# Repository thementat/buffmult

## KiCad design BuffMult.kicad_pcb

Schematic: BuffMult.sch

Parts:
C1, C2, C3, C4: 6p; C_0805_2012Metric
C5, C6, C7, C8, C9, C10, C11, C12, C13, C14, C15, C16: 10p; C_0805_2012Metric
C17, C22: 22u; CP_Elec_5x5.8
C18, C19, C20, C21, C23, C24, C25, C26: 100n; C_0805_2012Metric
D1, D2: 1N5819HW; D_SOD-123
J1, J2: Conn_01x01; PinHeader_1x01_P2.54mm_Vertical
J3: Conn_02x05_Odd_Even; PinHeader_2x05_P2.54mm_Vertical_SMD
JP1, JP2, JP3, JP4, JP5, JP6, JP7, JP8, JP9, JP10, JP11, JP12, JP13, JP14, JP15: SolderJumper; SolderJumper-2_P1.3mm_Open_TrianglePad1.0x1.5mm
R1, R2, R3, R4: 107k; C_0805_2012Metric
R5, R6, R7, R8: 100k; C_0805_2012Metric
R9, R10, R11, R12, R13, R14, R15, R16, R25, R26, R27, R28, R29, R30, R31, R32, R41, R42, R43, R44, R45, R46, R47, R48: 49.9k; C_0805_2012Metric
R17, R18, R19, R20, R33, R34, R35, R36, R49, R50, R51, R52: 301; C_0805_2012Metric
R21, R22, R23, R24, R37, R38, R39, R40, R53, R54, R55, R56: 13.3k; C_0805_2012Metric
RV1, RV2, RV3, RV4, RV5, RV6, RV7, RV8, RV9, RV10, RV11, RV12: R_POT_US; Potentiometer_Bourns_3296W_Vertical
U1: PJ-301BM; WQP-PJ301M-12_JACK
U2, U4, U6, U8: TL074; SOIC-14_3.9x8.7mm_P1.27mm
U3, U5, U7, U9, U10, U11, U12, U16, U20: PJ-301BM; PJ301M
U13, U14, U15, U17, U18, U19: PJ-301BM; PJ301M-NG

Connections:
+12V: C17.1, C18.1, C19.1, C20.1, C21.1, D1.1, U2.4 (V+), U4.4 (V+), U6.4 (V+), U8.4 (V+)
-12V: C22.2, C23.2, C24.2, C25.2, C26.2, D2.2, U2.11 (V-), U4.11 (V-), U6.11 (V-), U8.11 (V-)
Earth: C17.2, C18.2, C19.2, C20.2, C21.2, C22.1, C23.1, C24.1, C25.1, C26.1, J1.1, J2.1, J3.3, J3.4, J3.5, J3.6, J3.7, J3.8, R21.2, R22.2, R23.2, R24.2, R37.2, R38.2, R39.2, R40.2, R53.2, R54.2, R55.2, R56.2, U1.P$3, U2.3 (+), U2.5 (+), U2.10 (+), U2.12 (+), U3.P$3, U4.3 (+), U4.5 (+), U4.10 (+), U4.12 (+), U5.P$3, U6.3 (+), U6.5 (+), U6.10 (+), U6.12 (+), U7.P$3, U8.3 (+), U8.5 (+), U8.10 (+), U8.12 (+), U9.P$3, U10.P$3, U11.P$3, U12.P$3, U16.P$3, U20.P$3
unnamed: C1.1, R1.1, RV1.1, RV5.1, RV9.1, U2.14
unnamed: C1.2, R1.2, R5.1, U2.13 (-)
unnamed: C2.1, R2.1, RV2.1, RV6.1, RV10.1, U4.14
unnamed: C2.2, R2.2, R6.1, U4.13 (-)
unnamed: C3.1, R3.1, RV3.1, RV7.1, RV11.1, U6.14
unnamed: C3.2, R3.2, R7.1, U6.13 (-)
unnamed: C4.1, R4.1, RV4.1, RV8.1, RV12.1, U8.14
unnamed: C4.2, R4.2, R8.1, U8.13 (-)
unnamed: C5.1, R17.2, U2.1
unnamed: C5.2, R9.2, R13.1, U2.2 (-)
unnamed: C6.1, R18.2, U4.1
unnamed: C6.2, R10.2, R14.1, U4.2 (-)
unnamed: C7.1, R19.2, U6.1
unnamed: C7.2, R11.2, R15.1, U6.2 (-)
unnamed: C8.1, R20.2, U8.1
unnamed: C8.2, R12.2, R16.1, U8.2 (-)
unnamed: C9.1, R33.2, U2.8
unnamed: C9.2, R25.2, R29.1, U2.9 (-)
unnamed: C10.1, R34.2, U4.8
unnamed: C10.2, R26.2, R30.1, U4.9 (-)
unnamed: C11.1, R35.2, U6.8
unnamed: C11.2, R27.2, R31.1, U6.9 (-)
unnamed: C12.1, R36.2, U8.8
unnamed: C12.2, R28.2, R32.1, U8.9 (-)
unnamed: C13.1, R49.2, U2.7
unnamed: C13.2, R41.2, R45.1, U2.6 (-)
unnamed: C14.1, R50.2, U4.7
unnamed: C14.2, R42.2, R46.1, U4.6 (-)
unnamed: C15.1, R51.2, U6.7
unnamed: C15.2, R43.2, R47.1, U6.6 (-)
unnamed: C16.1, R52.2, U8.7
unnamed: C16.2, R44.2, R48.1, U8.6 (-)
unnamed: D1.2, J3.9, J3.10
unnamed: D2.1, J3.1, J3.2
unnamed: JP1.1, U19.P$2
unnamed: JP1.2, JP7.2, JP11.2, JP15.2, R8.2, U7.P$1
unnamed: JP2.1, U17.P$2
unnamed: JP3.1, U18.P$2
unnamed: JP4.1, R9.1, R17.1, U9.P$1
unnamed: JP5.1, R10.1, R18.1, U10.P$1
unnamed: JP6.1, R11.1, R19.1, U11.P$1
unnamed: JP7.1, R12.1, R20.1, U12.P$1
unnamed: JP8.1, R25.1, R33.1, U13.P$1
unnamed: JP9.1, R26.1, R34.1, U14.P$1
unnamed: JP10.1, R27.1, R35.1, U15.P$1
unnamed: JP3.2, JP6.2, JP10.2, JP14.2, R7.2, U5.P$1
unnamed: JP11.1, R28.1, R36.1, U16.P$1
unnamed: JP12.1, R41.1, R49.1, U17.P$1
unnamed: JP4.2, JP8.2, JP12.2, R5.2, U1.P$1
unnamed: JP13.1, R42.1, R50.1, U18.P$1
unnamed: JP2.2, JP5.2, JP9.2, JP13.2, R6.2, U3.P$1
unnamed: JP14.1, R43.1, R51.1, U19.P$1
unnamed: JP15.1, R44.1, R52.1, U20.P$1
unnamed: R13.2, RV1.2
unnamed: R14.2, RV2.2
unnamed: R15.2, RV3.2
unnamed: R16.2, RV4.2
unnamed: R21.1, RV1.3
unnamed: R22.1, RV2.3
unnamed: R23.1, RV3.3
unnamed: R24.1, RV4.3
unnamed: R29.2, RV5.2
unnamed: R30.2, RV6.2
unnamed: R31.2, RV7.2
unnamed: R32.2, RV8.2
unnamed: R37.1, RV5.3
unnamed: R38.1, RV6.3
unnamed: R39.1, RV7.3
unnamed: R40.1, RV8.3
unnamed: R45.2, RV9.2
unnamed: R46.2, RV10.2
unnamed: R47.2, RV11.2
unnamed: R48.2, RV12.2
unnamed: R53.1, RV9.3
unnamed: R54.1, RV10.3
unnamed: R55.1, RV11.3
unnamed: R56.1, RV12.3

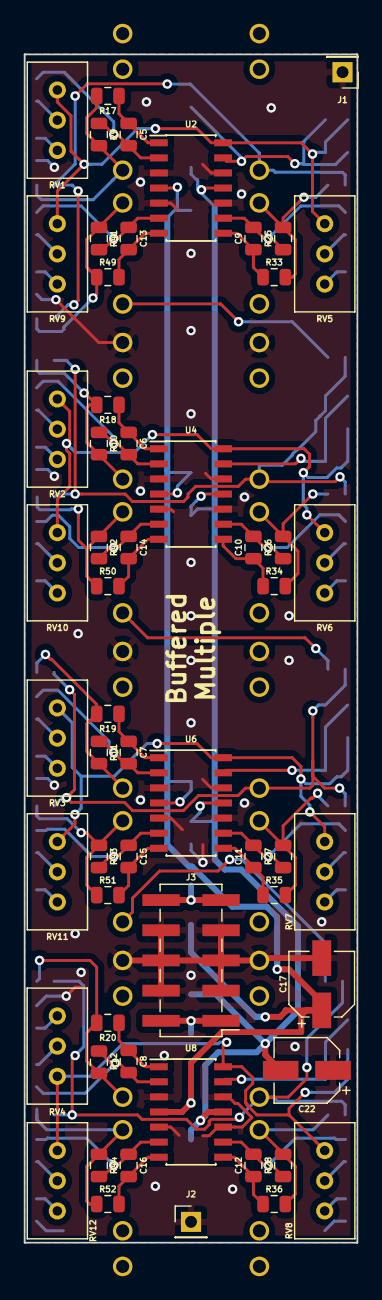
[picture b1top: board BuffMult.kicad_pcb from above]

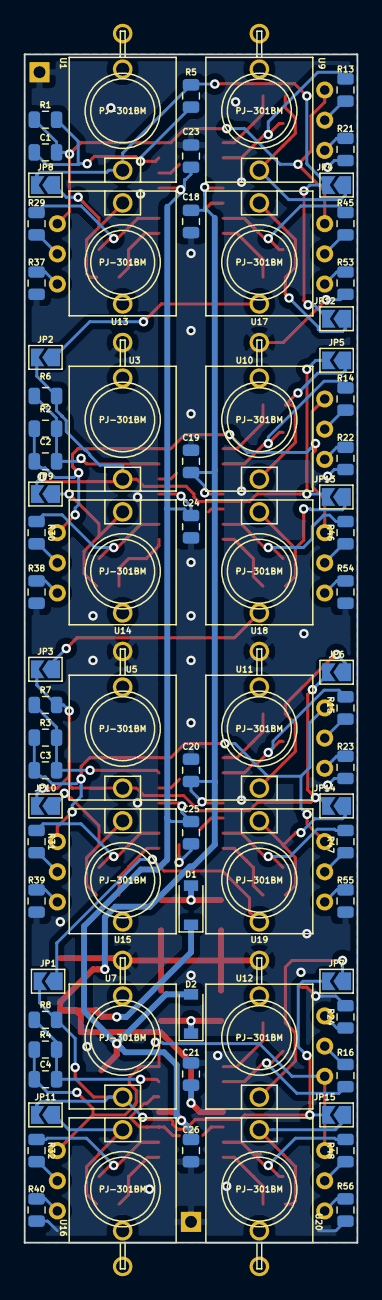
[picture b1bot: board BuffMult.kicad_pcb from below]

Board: 2 copper layers, 28.0 x 100.0 mm, 134 parts (77 on the bottom side), 80 nets.

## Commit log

2019-09-24 Updated
    Updated
